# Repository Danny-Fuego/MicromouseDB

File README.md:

# Micromouse
Micromouse PCB Design

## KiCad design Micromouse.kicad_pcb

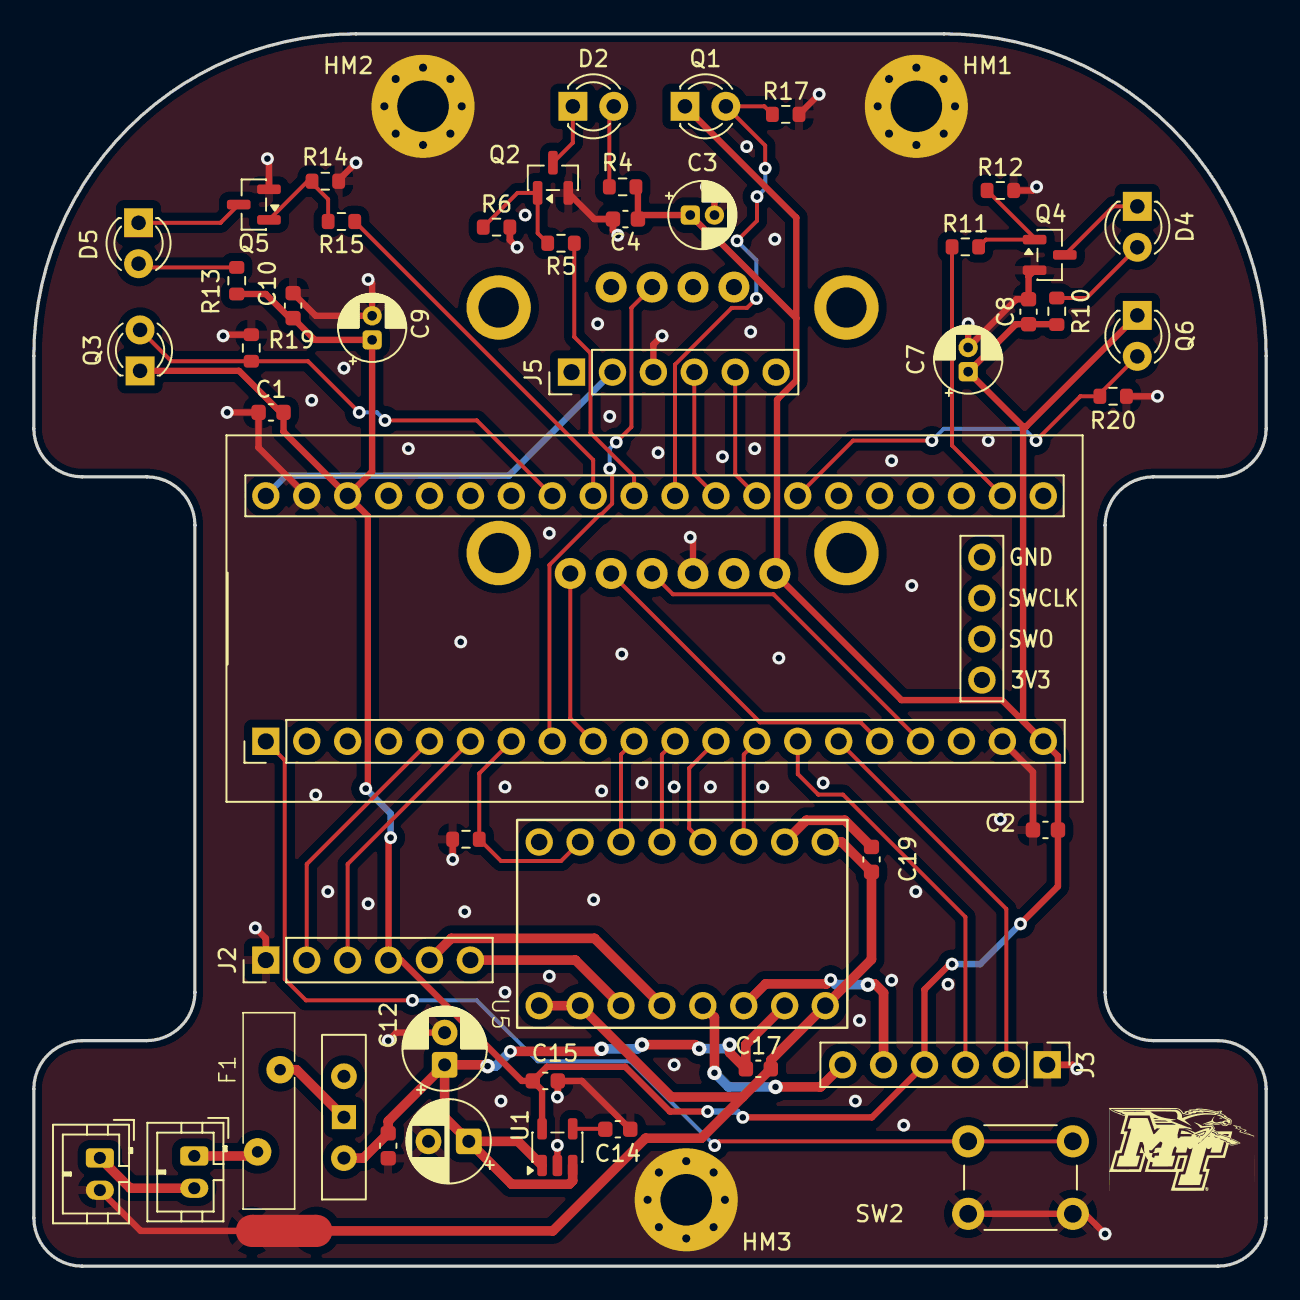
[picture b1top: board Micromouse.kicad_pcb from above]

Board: 2 copper layers, 76.5 x 76.5 mm, 53 parts (1 on the bottom side), 45 nets.

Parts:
A1: Adafruit_BNO055_Breakout; MODULE_2472
C1, C2, C11: 0.1 µF; C_0603_1608Metric
C3, C7, C9: 4.7uF; CP_Radial_D4.0mm_P1.50mm
C4, C8, C10: 0.1uF; C_0603_1608Metric
C12: 100 µF; CP_Radial_D5.0mm_P2.00mm
C13: 10uF; CP_Radial_D5.0mm_P2.50mm
C14: 1nF; C_0603_1608Metric
C15: 22uF; C_0603_1608Metric
C17: 10uF; C_0603_1608Metric
C19: 2.2uF; C_0603_1608Metric
D2, D4, D5: SFH4550; LED_D3.0mm_IRGrey
F1: MF-R185; Fuse_Bourns_MF-R185
HM1, HM2, HM3: MountingHole_3.2mm_M3_Pad_Via
J1, J4: Conn_01x02; JST_PH_B2B-PH-K_1x02_P2.00mm_Vertical
J2, J3, J5: Conn_01x06; PinHeader_1x06_P2.54mm_Vertical
NT1: NetTie_2; NetTie-2_SMD_Pad2.0mm
Q1, Q3, Q6: SFH309; LED_D3.0mm_IRBlack
Q2, Q4, Q5: Q_NMOS_GDS; SOT-23
R2: 10K; R_0603_1608Metric
R4, R10, R13: 10R; R_0603_1608Metric
R5, R11, R15: 100R; R_0603_1608Metric
R6, R12, R14, R17, R19, R20: 47K; R_0603_1608Metric
SW1: SW_SPDT; SW_Slide-03_Wuerth-WS-SLTV_10x2.5x6.4_P2.54mm
SW2: SW_Push; SW_PUSH_6mm
U1: MIC5219-3.3YM5; SOT-23-5
U4: STM32F11CE_BlackPill; YAAJ_BluePill_SWD_1
U5: DRV8833_BreakoutBoard

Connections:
5V: J5.2, U4.40 (5V)
+3V3: A1.1 (Vin), C1.2, C2.1, C3.1, C4.1, C7.1, C8.1, C9.1, C10.1, C15.1, J2.4, J3.4, Q1.1 (C), Q3.1 (C), Q6.1 (C), R4.1, R10.1, R13.1, U1.5 (OUT), U4.20 (3V3), U4.38 (3V3)
/Power/+BATT: J1.1, J4.2
/Power/+BATT_FUSED: F1.2, SW1.1 (A)
GND: A1.3 (GND), C1.1, C2.2, C3.2, C4.2, C7.2, C8.2, C9.2, C10.2, C11.1, C12.2, C13.2, C14.2, C15.2, HM1.1, HM2.1, HM3.1, J1.2, J2.1, J3.1, J5.3, NT1.1, Q2.2 (D), Q4.2 (D), Q5.2 (D), R2.1, R6.2, R12.2, R14.2, R17.2, R19.2, R20.2, SW2.2, U1.2 (GND), U4.19 (GND), U4.39 (GND)
MGND: C17.2, C19.1, NT1.2, U5.1 (BISEN), U5.3 (AISEN), U5.15 (GND), U5.16 (GND)
ML-1: J2.6, U5.5 (AOUT1)
ML-2: J2.5, U5.7 (AOUT2)
MR-1: J3.6, U5.9 (BOUT2)
MR-2: J3.5, U5.11 (BOUT1)
unnamed: D2.2 (A), R4.2
unnamed: D2.1 (K), Q2.3 (S)
unnamed: D4.2 (A), R10.2
unnamed: D4.1 (K), Q4.3 (S)
unnamed: D5.2 (A), R13.2
unnamed: D5.1 (K), Q5.3 (S)
unnamed: F1.1, J4.1
unnamed: Q2.1 (G), R5.2, R6.1
unnamed: Q4.1 (G), R11.2, R12.1
unnamed: Q5.1 (G), R14.1, R15.2
unnamed: C14.1, U1.4 (BP)
unnamed: C19.2, U5.14 (VMM)
PA1: Q6.2 (E), R20.1, U4.27 (PA1)
PA2: J5.5, U4.28 (PA2)
PA3: J5.4, U4.29 (PA3)
PA4: Q1.2 (E), R17.1, U4.30 (PA4)
PA5: R5.1, U4.31 (PA5)
PA6: R15.1, U4.32 (PA6)
PA7: Q3.2 (E), R19.1, U4.33 (PA7)
PA8: J2.2, U4.5 (PA8)
PA9: J2.3, U4.6 (PA9)
PA10: R2.2, U4.7 (PA10), U5.4 (~SLEEP)
PA11: A1.8 (INT), U4.8 (PA11)
PA12: A1.6 (RST), U4.9 (PA12)
PA15: U4.10 (PA15), U5.6 (AIN1)
PB3: U4.11 (PB3), U5.8 (AIN2)
PB4: U4.12 (PB4), U5.10 (BIN2)
PB5: U4.13 (PB5), U5.12 (BIN1)
PB6: J3.3, U4.14 (PB6)
PB7: J3.2, U4.15 (PB7)
PB8: A1.5 (SCL), U4.16 (PB8)
PB9: A1.4 (SDA), U4.17 (PB9)
PB12: SW2.1, U4.1 (PB12)
PC13: R11.1, U4.22 (PC13)
VBATT_SW: C11.2, C12.1, C13.1, C17.1, SW1.2 (B), U1.1 (IN), U1.3 (EN), U5.13 (VIN)

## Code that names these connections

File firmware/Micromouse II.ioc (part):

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Mcu.Name=STM32F411C(C-E)Ux
Mcu.Package=UFQFPN48
Mcu.UserName=STM32F411CEUx
PA1.GPIOParameters=GPIO_Label
PA1.GPIO_Label=IR_RECEIVER_R
PA1.Signal=ADCx_IN1
PA10.GPIOParameters=GPIO_PuPd,GPIO_Label
PA10.GPIO_Label=MOTOR_SLEEP
PA10.GPIO_PuPd=GPIO_NOPULL
PA10.Signal=GPIO_Output
PA11.GPIOParameters=GPIO_Label
PA11.GPIO_Label=GYRO_INT
PA11.Signal=GPXTI11
PA12.GPIOParameters=GPIO_Speed,PinState,GPIO_Label
PA12.GPIO_Label=GYRO_RST
PA12.GPIO_Speed=GPIO_SPEED_FREQ_MEDIUM
PA12.PinState=GPIO_PIN_SET
PA12.Signal=GPIO_Output
PA15.GPIOParameters=GPIO_Speed,GPIO_Label
PA15.GPIO_Label=MOTOR_LEFT_IN1
PA15.GPIO_Speed=GPIO_SPEED_FREQ_VERY_HIGH
PA15.Signal=S_TIM2_CH1_ETR
PA2.Mode=Asynchronous
PA2.Signal=USART2_TX
PA3.Mode=Asynchronous
PA3.Signal=USART2_RX
PA4.GPIOParameters=GPIO_Label
PA4.GPIO_Label=IR_RECEIVER_F
PA4.Signal=ADCx_IN4
PA5.GPIOParameters=GPIO_Speed,GPIO_Label
PA5.GPIO_Label=IR_EMITTER_F
PA5.GPIO_Speed=GPIO_SPEED_FREQ_MEDIUM
PA5.Signal=GPIO_Output
PA6.GPIOParameters=GPIO_Speed,GPIO_Label
PA6.GPIO_Label=IR_EMITTER_L
PA6.GPIO_Speed=GPIO_SPEED_FREQ_MEDIUM
PA6.Signal=GPIO_Output
PA7.GPIOParameters=GPIO_Label
PA7.GPIO_Label=IR_RECEIVER_L
PA7.Signal=ADCx_IN7
PA8.GPIOParameters=GPIO_Label
PA8.GPIO_Label=ENCODER_LEFT_B
PA8.Signal=S_TIM1_CH1
PA9.GPIOParameters=GPIO_Label
PA9.GPIO_Label=ENCODER_LEFT_A
PA9.Signal=S_TIM1_CH2
PB12.GPIOParameters=GPIO_PuPd,GPIO_Label
PB12.GPIO_Label=BUTTON
PB12.GPIO_PuPd=GPIO_PULLUP
PB12.Signal=GPIO_Input
PB3.GPIOParameters=GPIO_Speed,GPIO_Label
PB3.GPIO_Label=MOTOR_LEFT_IN2
PB3.GPIO_Speed=GPIO_SPEED_FREQ_VERY_HIGH
PB3.Signal=S_TIM2_CH2
PB4.GPIOParameters=GPIO_Speed,GPIO_Label
PB4.GPIO_Label=MOTOR_RIGHT_IN1
PB4.GPIO_Speed=GPIO_SPEED_FREQ_VERY_HIGH
PB4.Signal=S_TIM3_CH1
PB5.GPIOParameters=GPIO_Speed,GPIO_Label
PB5.GPIO_Label=MOTOR_RIGHT_IN2
PB5.GPIO_Speed=GPIO_SPEED_FREQ_VERY_HIGH
PB5.Signal=S_TIM3_CH2
PB6.GPIOParameters=GPIO_Label
PB6.GPIO_Label=ENCODER_RIGHT_A
PB6.Signal=S_TIM4_CH1
PB7.GPIOParameters=GPIO_Label
PB7.GPIO_Label=ENCODER_RIGHT_B
PB7.Signal=S_TIM4_CH2
PB8.GPIOParameters=GPIO_Label
PB8.GPIO_Label=GYRO_SCL
PB8.Mode=I2C
PB8.Signal=I2C1_SCL
PB9.GPIOParameters=GPIO_Label
PB9.GPIO_Label=GYRO_SDA
PB9.Mode=I2C
PB9.Signal=I2C1_SDA
PC13-ANTI_TAMP.GPIOParameters=GPIO_Label
PC13-ANTI_TAMP.GPIO_Label=IR_EMITTER_R
PC13-ANTI_TAMP.Signal=GPIO_Output
RCC.HSE_VALUE=25000000
RCC.SYSCLKFreq_VALUE=84000000
RCC.SYSCLKSource=RCC_SYSCLKSOURCE_PLLCLK
board=custom
